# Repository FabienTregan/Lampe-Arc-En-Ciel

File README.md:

# Lampe-Arc-En-Ciel
A rainbow lamp with SK9822 and ATMega328PB (arduino compatible)

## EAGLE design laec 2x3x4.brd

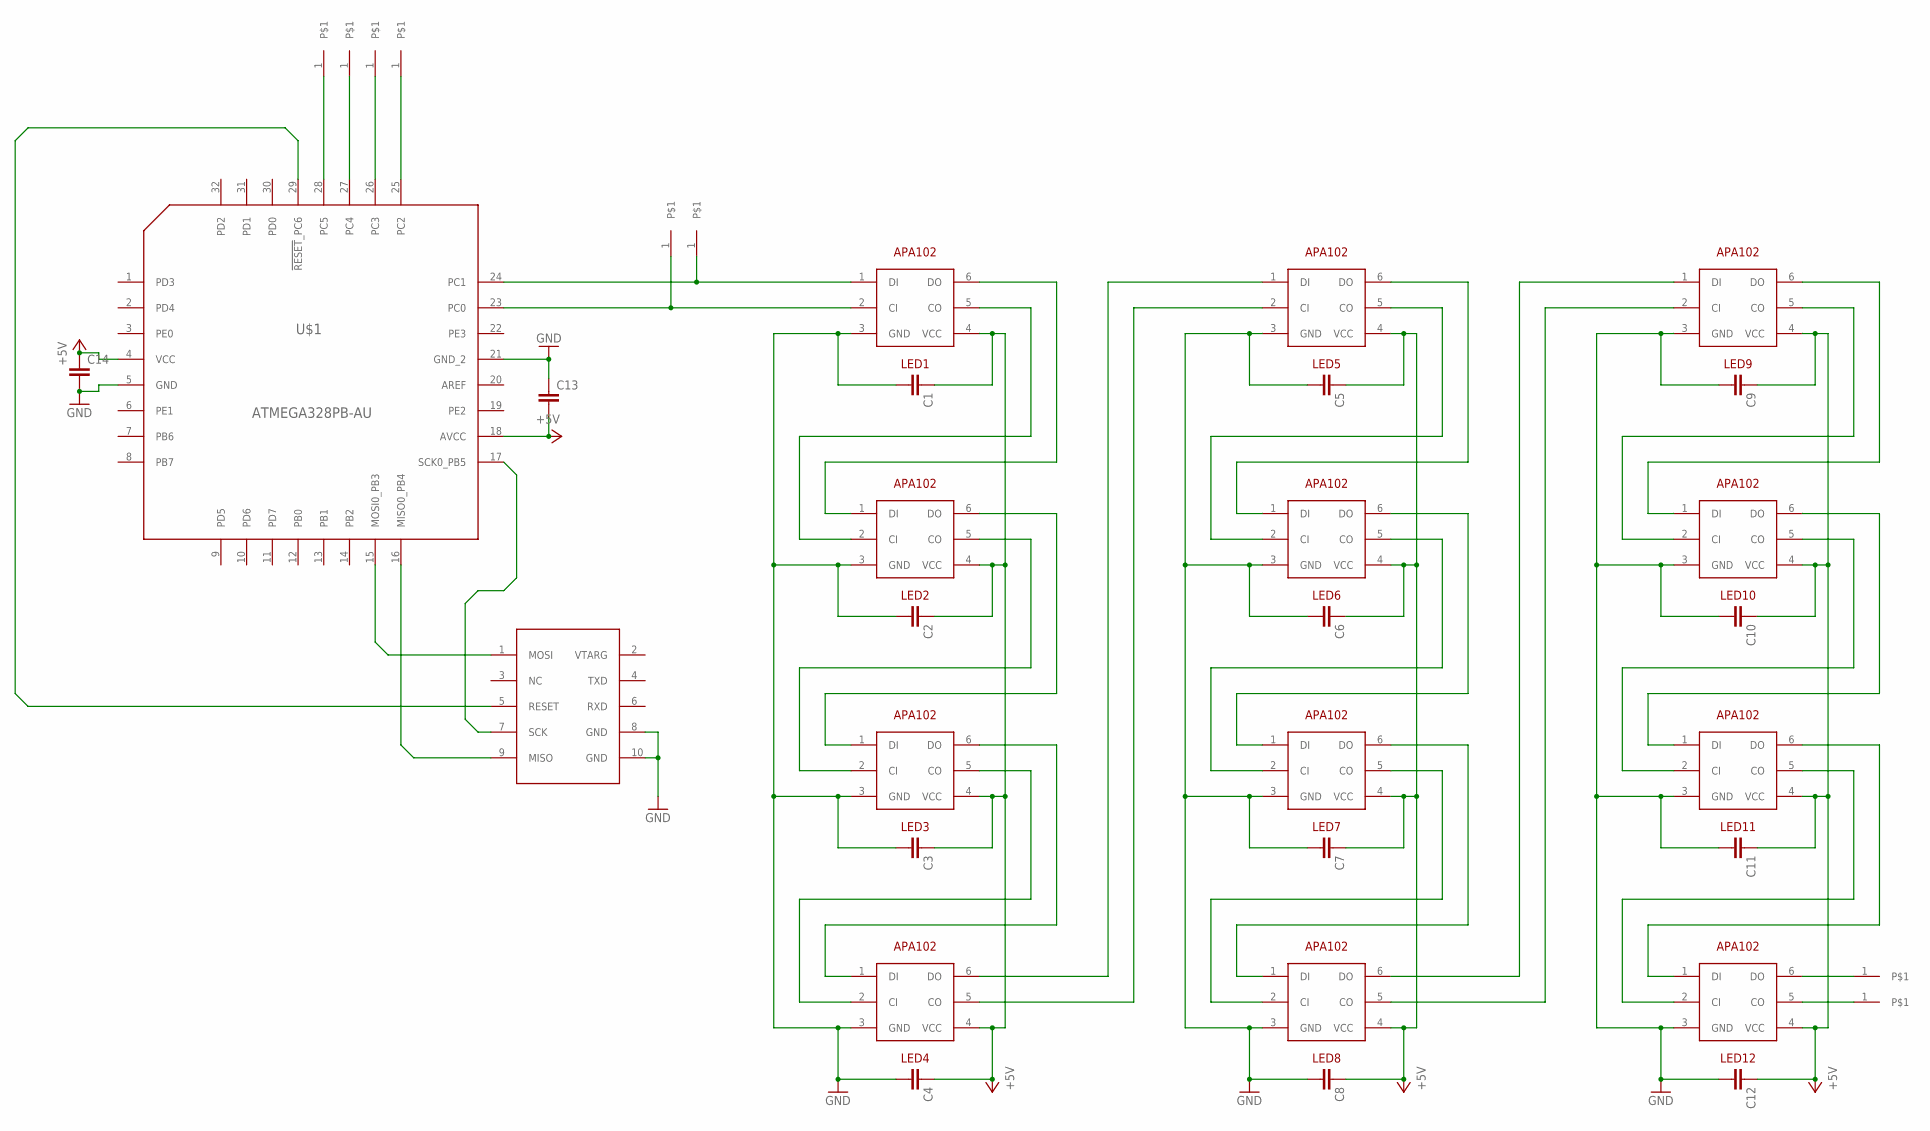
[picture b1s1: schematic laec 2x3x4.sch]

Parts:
BOARD_CI: CI; 37MIL_HOLE
BOARD_CO: CO; 37MIL_HOLE
BOARD_DI: DI; 37MIL_HOLE
BOARD_DO: DO; 37MIL_HOLE
C1, C2, C3, C4, C5, C6, C7, C8, C9, C10, C11, C12, C13, C14: C; C0805
LED1, LED2, LED3, LED4, LED5, LED6, LED7, LED8, LED9, LED10, LED11, LED12: APA102; 5050
TOUCH_1, TOUCH_2, TOUCH_3, TOUCH_4: CAP_TOUCH_12MM_ROUND; 12MM_ROUND
U$1: ATMEGA328PB-AU; QFP80P900X900X120-32N
U$2: AVR_ISP_10; AVR_ISP_2X5

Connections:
+5V: C1.1, C2.1, C3.1, C4.1, C5.1, C6.1, C7.1, C8.1, C9.1, C10.1, C11.1, C12.1, C13.2, C14.1, LED1.4 (VCC), LED2.4 (VCC), LED3.4 (VCC), LED4.4 (VCC), LED5.4 (VCC), LED6.4 (VCC), LED7.4 (VCC), LED8.4 (VCC), LED9.4 (VCC), LED10.4 (VCC), LED11.4 (VCC), LED12.4 (VCC), U$1.4 (VCC), U$1.18 (AVCC)
GND: C1.2, C2.2, C3.2, C4.2, C5.2, C6.2, C7.2, C8.2, C9.2, C10.2, C11.2, C12.2, C13.1, C14.2, LED1.3 (GND), LED2.3 (GND), LED3.3 (GND), LED4.3 (GND), LED5.3 (GND), LED6.3 (GND), LED7.3 (GND), LED8.3 (GND), LED9.3 (GND), LED10.3 (GND), LED11.3 (GND), LED12.3 (GND), U$1.5 (GND), U$1.21 (GND_2), U$2.8 (GND), U$2.10 (GND)
unnamed: LED1.6 (DO), LED2.1 (DI)
unnamed: LED1.5 (CO), LED2.2 (CI)
unnamed: LED4.5 (CO), LED5.2 (CI)
unnamed: LED8.6 (DO), LED9.1 (DI)
unnamed: LED2.6 (DO), LED3.1 (DI)
unnamed: LED2.5 (CO), LED3.2 (CI)
unnamed: U$1.15 (MOSI0_PB3), U$2.1 (MOSI)
unnamed: U$1.16 (MISO0_PB4), U$2.9 (MISO)
unnamed: LED3.6 (DO), LED4.1 (DI)
unnamed: LED3.5 (CO), LED4.2 (CI)
unnamed: TOUCH_1.1, U$1.25 (PC2)
unnamed: U$1.17 (SCK0_PB5), U$2.7 (SCK)
unnamed: LED4.6 (DO), LED5.1 (DI)
unnamed: U$1.29 (!RESET!_PC6), U$2.5 (RESET)
unnamed: LED9.6 (DO), LED10.1 (DI)
unnamed: LED9.5 (CO), LED10.2 (CI)
unnamed: LED5.6 (DO), LED6.1 (DI)
unnamed: LED5.5 (CO), LED6.2 (CI)
unnamed: TOUCH_2.1, U$1.26 (PC3)
unnamed: TOUCH_4.1, U$1.28 (PC5)
unnamed: LED6.6 (DO), LED7.1 (DI)
unnamed: LED6.5 (CO), LED7.2 (CI)
unnamed: TOUCH_3.1, U$1.27 (PC4)
unnamed: BOARD_DO.1, LED12.6 (DO)
unnamed: LED7.6 (DO), LED8.1 (DI)
unnamed: LED7.5 (CO), LED8.2 (CI)
unnamed: BOARD_CO.1, LED12.5 (CO)
unnamed: LED10.6 (DO), LED11.1 (DI)
unnamed: LED10.5 (CO), LED11.2 (CI)
unnamed: LED11.6 (DO), LED12.1 (DI)
unnamed: LED11.5 (CO), LED12.2 (CI)
unnamed: LED8.5 (CO), LED9.2 (CI)
unnamed: BOARD_DI.1, LED1.1 (DI), U$1.24 (PC1)
unnamed: BOARD_CI.1, LED1.2 (CI), U$1.23 (PC0)

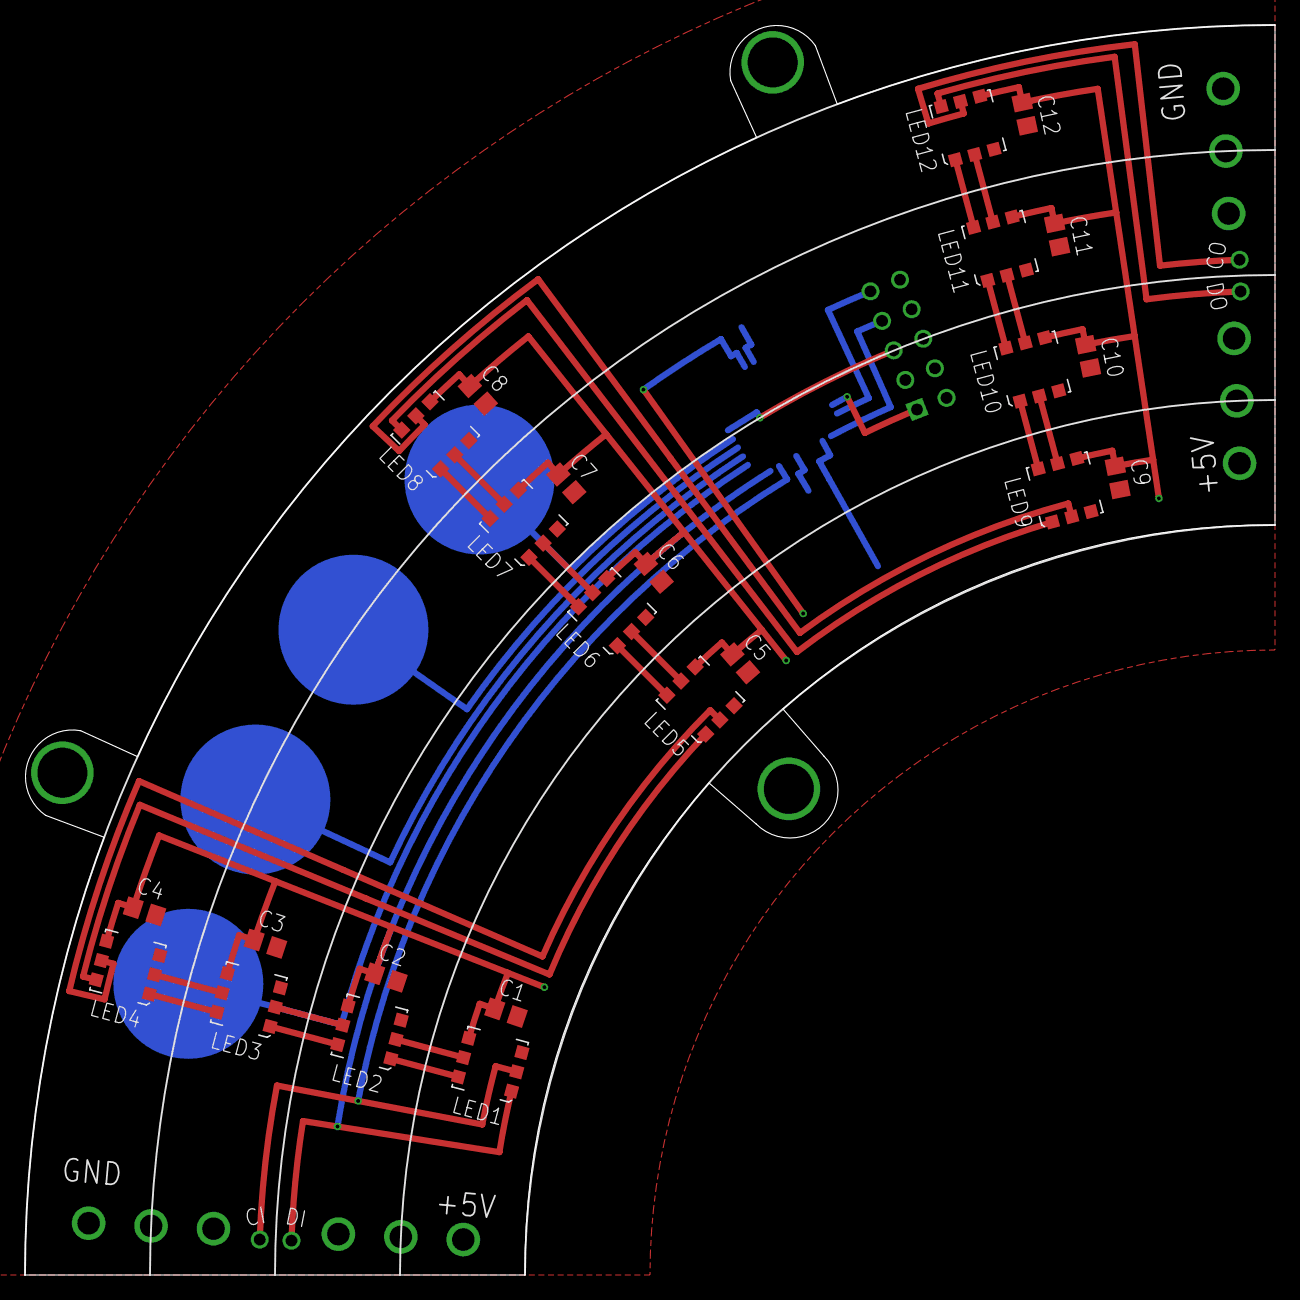
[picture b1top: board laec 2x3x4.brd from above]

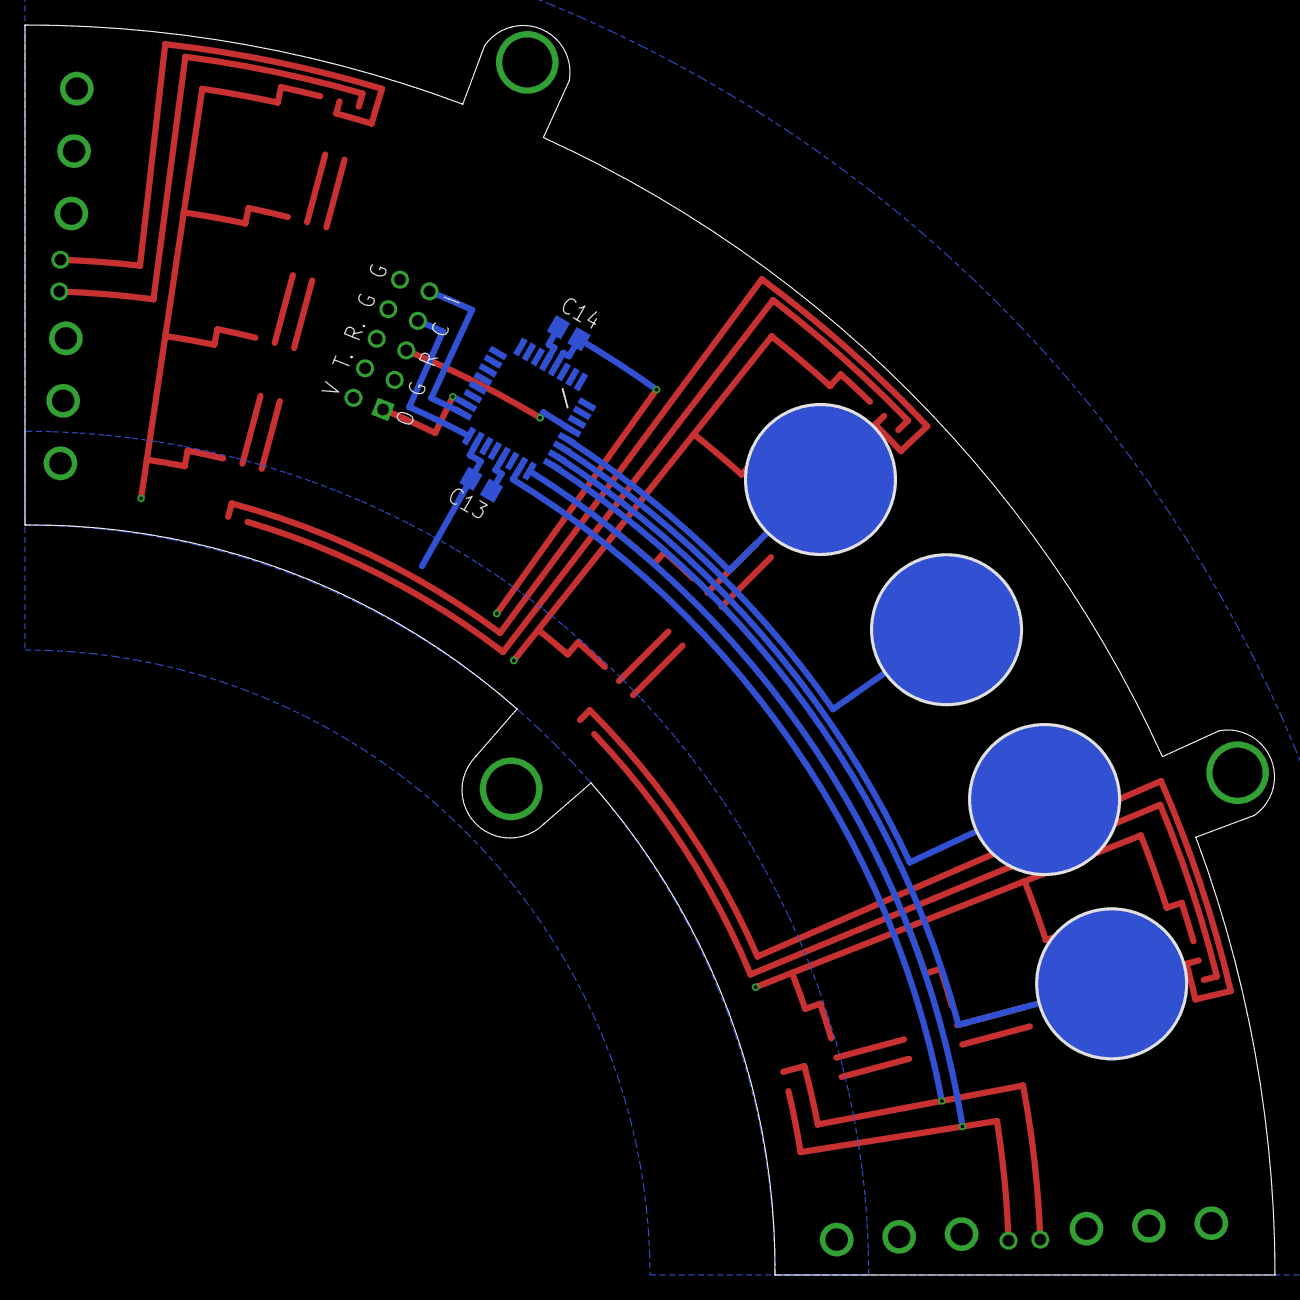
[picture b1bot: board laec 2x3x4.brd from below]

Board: 2 copper layers, 100.0 x 100.0 mm, 36 parts (8 on the bottom side), 36 nets.

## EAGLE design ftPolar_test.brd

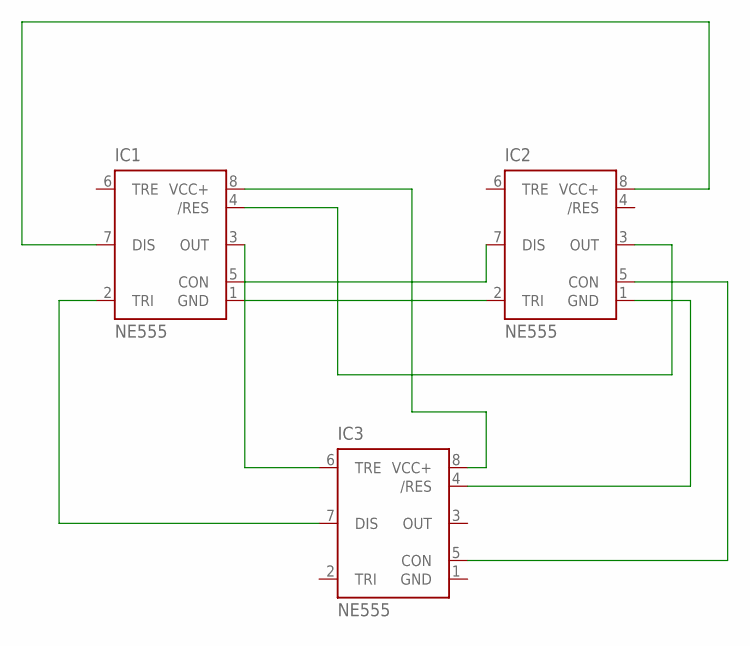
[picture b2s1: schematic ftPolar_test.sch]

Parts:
IC1, IC2, IC3: NE555; DIL-08

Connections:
GND: IC3.1 (GND)
unnamed: IC1.1 (GND), IC2.2 (TRI)
unnamed: IC1.5 (CON), IC2.7 (DIS)
unnamed: IC1.3 (OUT), IC3.6 (TRE)
unnamed: IC1.8 (VCC+), IC3.8 (VCC+)
unnamed: IC1.4 (/RES), IC2.3 (OUT)
unnamed: IC1.2 (TRI), IC3.7 (DIS)
unnamed: IC1.7 (DIS), IC2.8 (VCC+)
unnamed: IC2.5 (CON), IC3.5 (CON)
unnamed: IC2.1 (GND), IC3.4 (/RES)

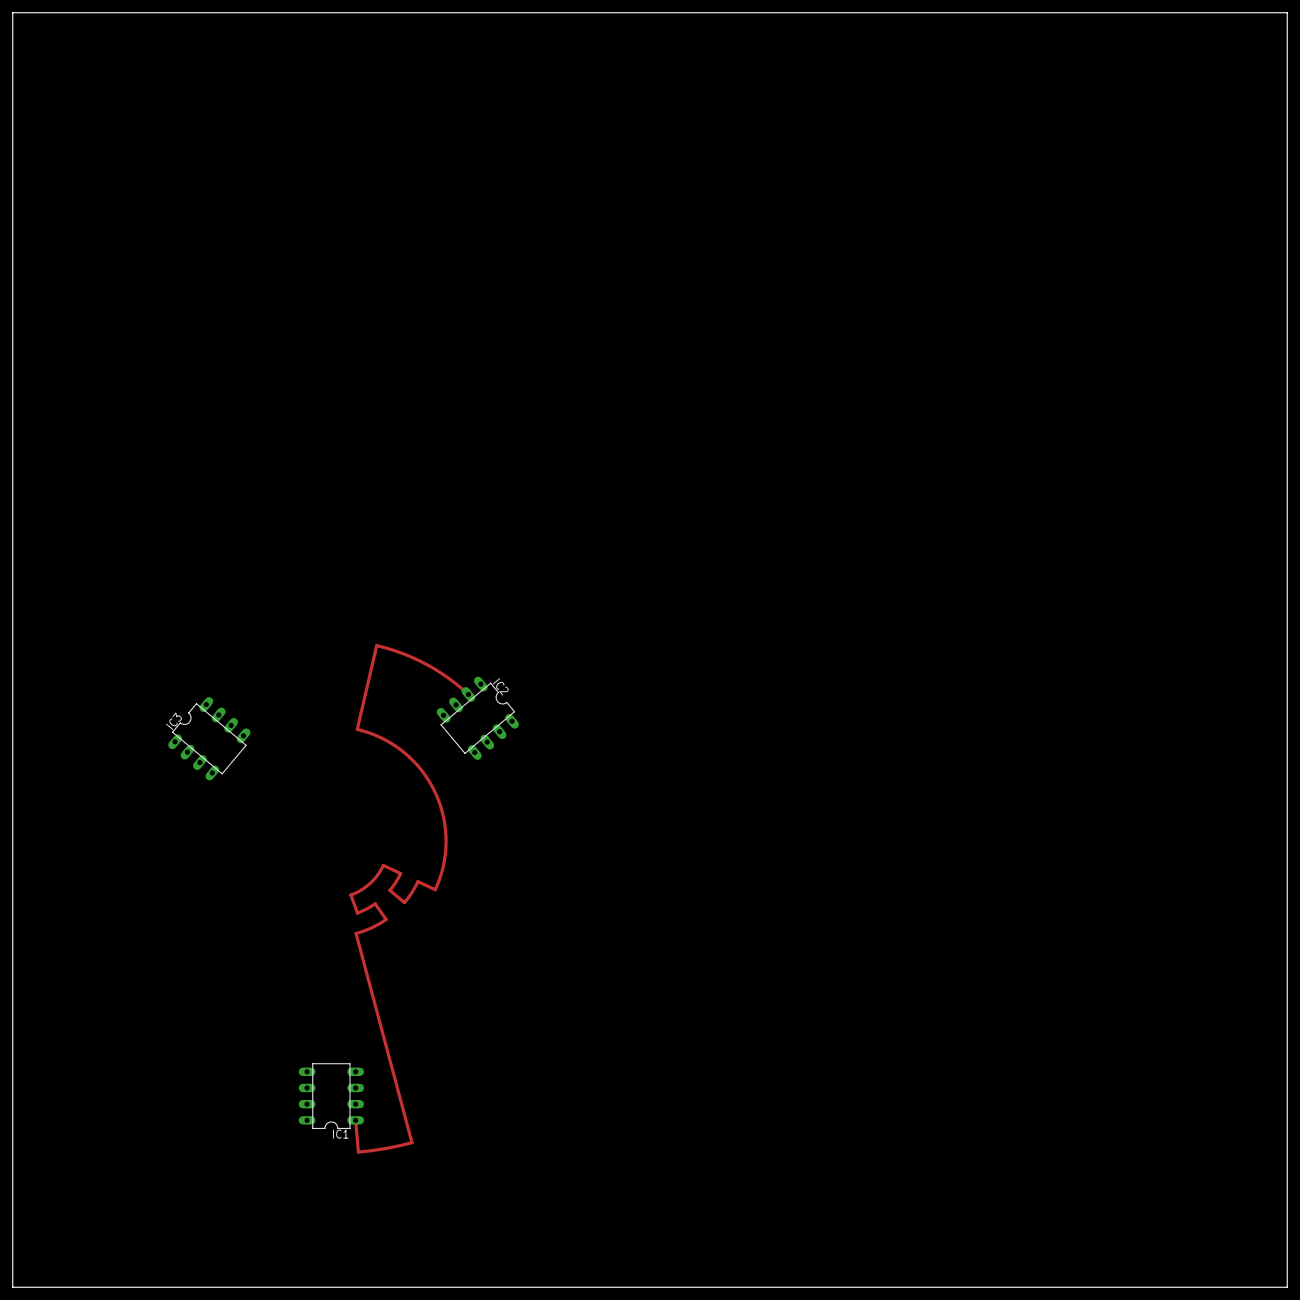
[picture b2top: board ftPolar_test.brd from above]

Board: 2 copper layers, 200.0 x 200.0 mm, 3 parts (0 on the bottom side), 9 nets.

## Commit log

2018-07-30 Adds existing local files.
2018-08-01 Adds the ftPolar library.
2018-08-01 Extracts the findXxx function in a separate lib.
2018-08-01 Uses ftPolar to connect caps.
2018-08-01 Wires clock and data from end of segment to start of next one.
2018-08-02 Changes width of segments connections to 0.5mm.
2018-08-02 Adds vias for the caps (easy side only).
2018-08-02 Adds missing vias for the caps.
2018-08-02 Renames connectLeds to connectRows.
2018-08-03 Extracts the markCenter() function.
2018-08-04 Switches to one ground plane on each side, routes every component !
2018-08-05 Corrects all DRC errors.
2018-08-05 Makes connection between segments closer.
2018-08-07 Parameterizes mcu's segment.
2018-08-07 Adds capacitiv touch bouttons.
2018-08-09 Adds DO and CO connection on exit end of the PCB.
2018-08-10 Splits ftpStart() into ftpStart() and ftpJump() + saves scripts in files.
2018-08-10 Allows to find contact by element name and contact name.
2018-08-10 Completes boards connection.
2018-08-10 Better positions the via from caps to +5v.
2018-08-10 Changes width of buttons silkscreen, better positions board CI DI CO DO.
2018-08-12 Adds screw tabs.
2018-08-12 Labels +5V and GND board connections.
